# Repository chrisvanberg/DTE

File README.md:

___
# DTE ( Digital Temperature Equipment )
[EPHEC](http://www.ephec.be/cours-du-jours/nos-formations/informatique-3) - 2016/17 - T207 Digital Electronics, signal management. - Group 05

## Team
- **Chris Van Waesberghe** ([contact@chris.be](mailto:contact@chrisv.be)) - JAVA
- **Nathan Dolinski** ([n.dolinski@students.ephec.be](n.dolinski@students.ephec.be)) - PROTEUS / EAGLE
- **Mathieu Rousseau** ([m.rousseau@students.ephec.be](m.rousseau@students.ephec.be)) - PROTEUS / EAGLE / CCS
- **Amélie Courtin** ([a.courtin@students.ephec.be](a.courtin@students.ephec.be)) - WELDS / JAVA

## Warning
**Digital Temperature Equipment** was a school project (2016/17). It may never be updated in the future. Use it a your own risk. However feel free to submit a pull request !

## How to launch the simulation
1. Prerequisites
    1. The latest [JAVA runtime](https://www.java.com/fr/download/) update installed
    1. [Proteus 8](https://www.labcenter.com/)
1. Preset
    1. Clone or download the project
    1. Build or [download](https://github.com/KeydownR/DTE/releases) the binaries of the DTE JAVA interface
    1. Download and install the [**RXTX library**](http://fizzed.com/oss/rxtx-for-java) on your computer
    1. Create a COM virtual pair (Ex. COM1<->COM2) using for example [**VSPE** (Windows)](http://www.lawyerment.com/downloads/Programming/Debugging_and_Tracing/Review_17462_index.htm)
1. Launching the simulation
    1. Launch the DTE Java interface
    1. Connect to one of the COM port that you have paired earlier
    1. Open the PROTEUS project
    1. Be sure that the PIC source code is `sonde2.hex` (Double clic on the PIC and check the value)
    1. Click on the RS232 connector and selec the other COM port that you have paired earlier
    1. Start the PROTEUS simulation
1. Test the simulation
    1. You can change the threshold temperature on the JAVA interface
    1. You can change the current temperature on PROTEUS by clicking on the `+ / -` near the temperature probe
    1. The green led indicate that everything is fine
    1. The blinking red led indicate that the current temperature is beyond the threshold and an alert is triggered

## Licence

Copyright 2017
- [**Chris Van Waesberghe**](mailto:contact@chrisv.be) - JAVA
- [**Nathan Dolinski**](mailto:n.dolinski@students.ephec.be) - PROTEUS / EAGLE
- [**Mathieu Rousseau**](mailto:m.rousseau@students.ephec.be) - PROTEUS / EAGLE / CCS
- [**Amélie Courtin**](mailto:a.courtin@students.ephec.be) - WELDS / JAVA

The DTE Java Interface (and other components of the project) are free software: you can redistribute it and/or modify it under the terms of the GNU General Public License as published by the Free Software Foundation, either version 3 of the License, or (at your option) any later version. The DTE Java Interface is distributed in the hope that it will be useful, but WITHOUT ANY WARRANTY; without even the implied warranty of MERCHANTABILITY or FITNESS FOR A PARTICULAR PURPOSE.  See the GNU General Public License for more details.

You should have received a copy of the GNU General Public License along with the DTE Java Interface and the whole DTE Project.  If not, see <http://www.gnu.org/licenses/>.

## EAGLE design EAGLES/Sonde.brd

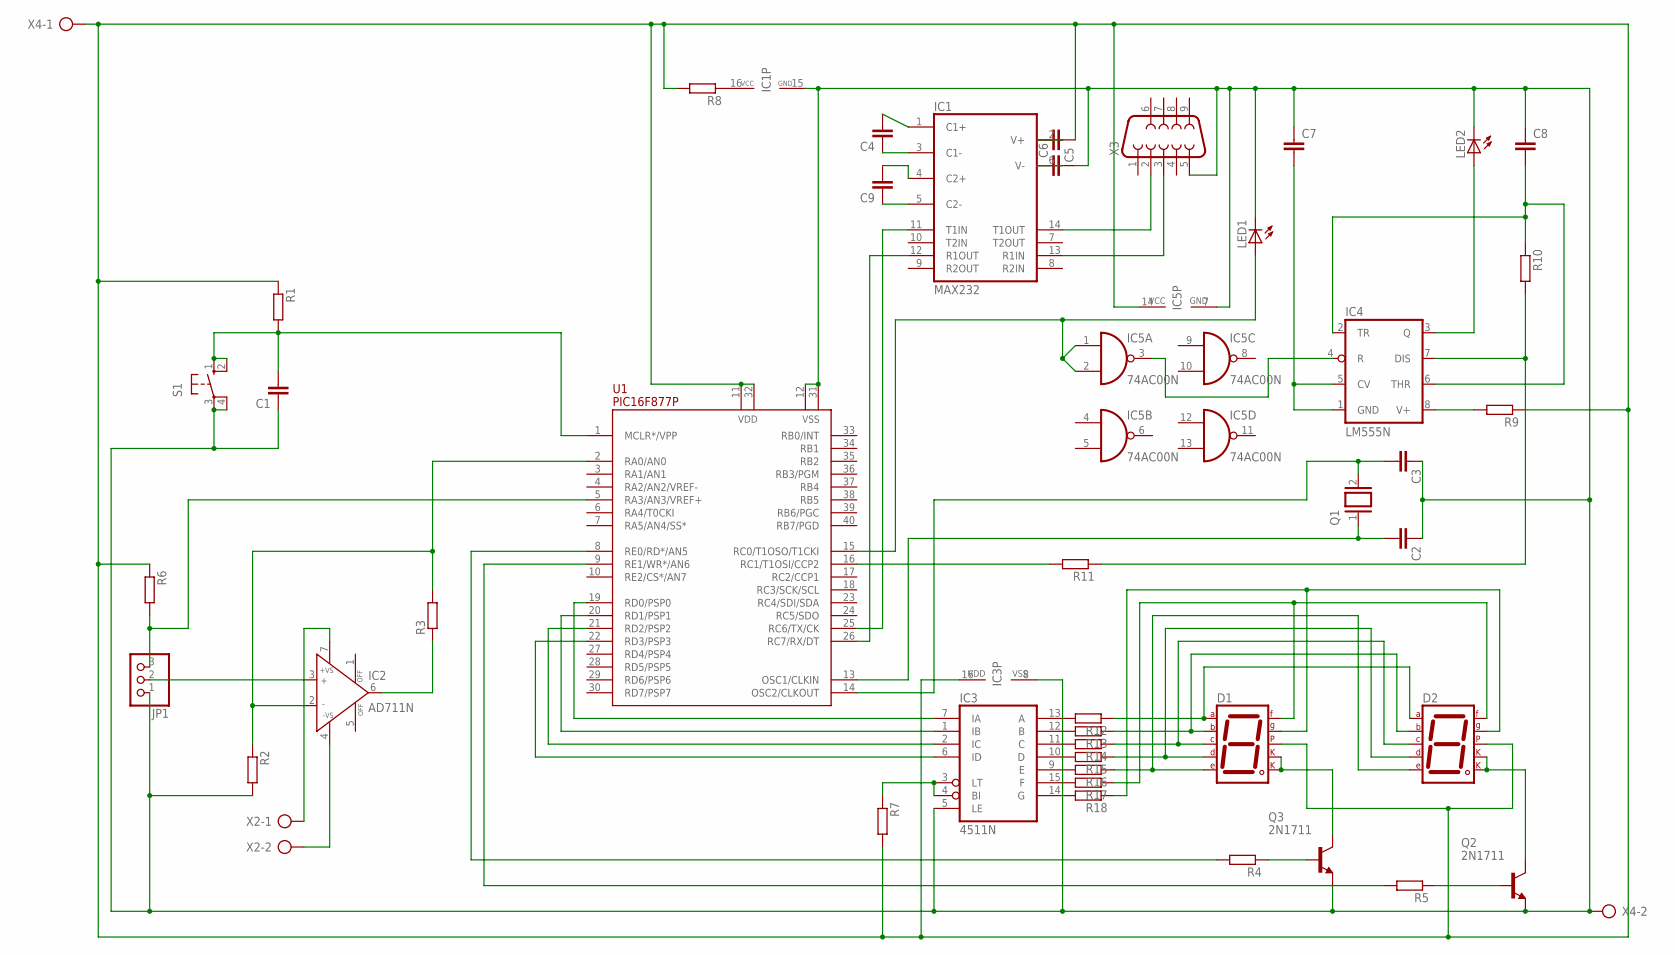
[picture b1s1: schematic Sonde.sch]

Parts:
C1, C2, C3, C4, C5, C6, C7, C8, C9: C-EU025-024X044; C025-024X044
D1, D2: 7SEG-CK; 7SEG-13
IC1: MAX232; DIL16
IC2: AD711N; DIL08
IC3: 4511N; DIL16
IC4: LM555N; DIL08
IC5: 74AC00N; DIL14
JP1: PINHD-1X3; 1X03
LED1, LED2: LED_ELD260; LED_LD260
Q1: XTAL/S; QS
Q2, Q3: 2N1711; TO39
R1, R2, R3, R4, R5, R6, R7, R8, R9, R10, R11, R12, R13, R14, R15, R16, R17, R18: R-EU_0207/10; 0207/10
S1: 10-XX; B3F-10XX
U1: PIC16F877P; DIL40
X2, X4: AK300/2
X3: F09V

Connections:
GND: C1.1, C2.1, C3.1, C6.2, C7.1, C8.1, IC1.15 (GND), IC3.5 (LE), IC3.8 (VSS), IC5.7 (GND), JP1.1, LED1.K (C), LED2.K (C), Q2.1 (E), Q3.1 (E), R2.2, S1.3, S1.4 (P1), U1.12 (VSS), U1.31 (VSS), X3.5, X4.2
unnamed: IC1.13 (R1IN), X3.3
unnamed: D2.3 (CK1), D2.8 (CK2), Q2.3 (C)
unnamed: IC4.4 (R), IC5.3 (O)
unnamed: C2.2, Q1.1, U1.13 (OSC1/CLKIN)
unnamed: IC2.3 (IN+), JP1.2
unnamed: D1.3 (CK1), D1.8 (CK2), Q3.3 (C)
unnamed: IC2.2 (IN-), R2.1, R3.2, U1.2 (RA0/AN0)
unnamed: Q3.2 (B), R4.1
unnamed: Q2.2 (B), R5.1
unnamed: R4.2, U1.8 (RE0/RD*/AN5)
unnamed: R5.2, U1.9 (RE1/WR*/AN6)
unnamed: D1.7 (A), D2.7 (A), R12.1
unnamed: C5.2, IC1.2 (V+)
unnamed: D1.6 (B), D2.6 (B), R13.1
unnamed: D1.4 (C), D2.4 (C), R14.1
unnamed: D1.2 (D), D2.2 (D), R15.1
unnamed: D1.1 (E), D2.1 (E), R16.1
unnamed: C6.1, IC1.6 (V-)
unnamed: D1.9 (F), D2.9 (F), R17.1
unnamed: IC1.11 (T1IN), U1.25 (RC6/TX/CK)
unnamed: D1.10 (G), D2.10 (G), R18.1
unnamed: IC1.12 (R1OUT), U1.26 (RC7/RX/DT)
unnamed: IC2.4 (-VS), X2.2
unnamed: IC2.6 (OUT), R3.1
unnamed: C9.2, IC1.4 (C2+)
unnamed: IC3.3 (LT), IC3.4 (BI), R7.1
unnamed: IC1.14 (T1OUT), X3.2
unnamed: IC3.7 (IA), U1.19 (RD0/PSP0)
unnamed: IC3.1 (IB), U1.20 (RD1/PSP1)
unnamed: IC3.2 (IC), U1.21 (RD2/PSP2)
unnamed: IC3.6 (ID), U1.22 (RD3/PSP3)
unnamed: C4.1, IC1.3 (C1-)
unnamed: C4.2, IC1.1 (C1+)
unnamed: R11.2, U1.16 (RC1/T1OSI/CCP2)
unnamed: IC1.16 (VCC), R8.1
unnamed: C7.2, IC4.1 (GND), IC4.5 (CV)
unnamed: IC4.8 (V+), R9.2
unnamed: IC4.3 (Q), LED2.A
unnamed: C1.2, R1.2, S1.1 (S), S1.2 (S1), U1.1 (MCLR*/VPP)
unnamed: C3.2, Q1.2, U1.14 (OSC2/CLKOUT)
unnamed: IC2.7 (+VS), X2.1
unnamed: C5.1, D1.5 (DP), D2.5 (DP), IC3.16 (VDD), IC5.14 (VCC), R1.1, R6.1, R7.2, R8.2, R9.1, U1.11 (VDD), U1.32 (VDD), X4.1
unnamed: C9.1, IC1.5 (C2-)
unnamed: IC3.13 (A), R12.2
unnamed: IC3.12 (B), R13.2
unnamed: IC3.11 (C), R14.2
unnamed: IC3.10 (D), R15.2
unnamed: IC3.9 (E), R16.2
unnamed: IC3.15 (F), R17.2
unnamed: IC3.14 (G), R18.2
unnamed: JP1.3, R6.2, U1.5 (RA3/AN3/VREF+)
unnamed: IC4.7 (DIS), R10.2, R11.1
unnamed: IC5.1 (I0), IC5.2 (I1), LED1.A, U1.15 (RC0/T1OSO/T1CKI)
unnamed: C8.2, IC4.2 (TR), IC4.6 (THR), R10.1

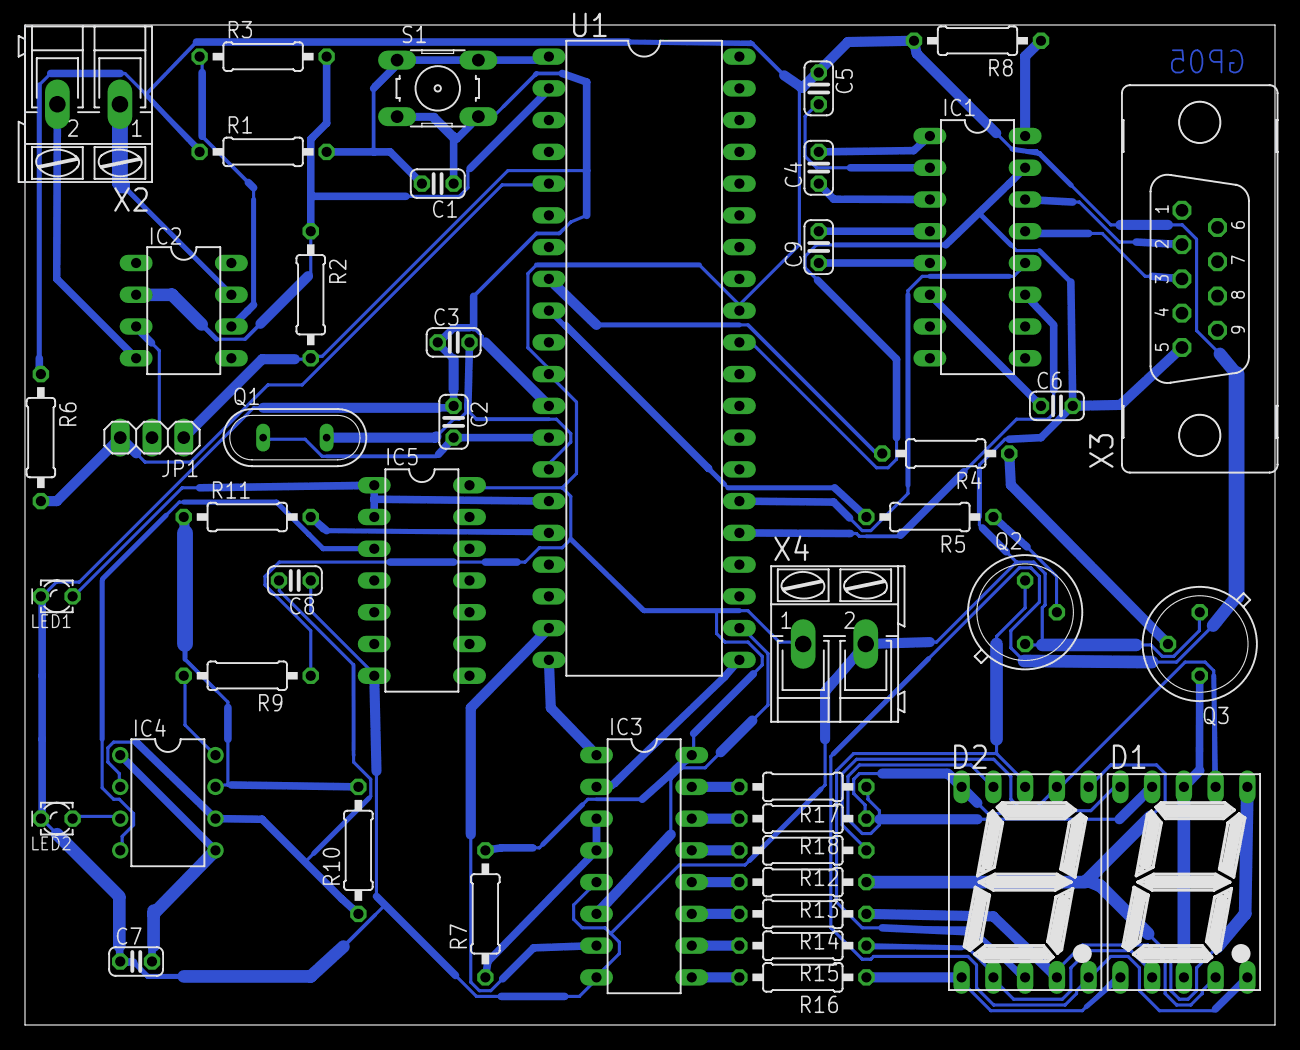
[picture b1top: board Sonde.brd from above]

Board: 2 copper layers, 100.0 x 80.0 mm, 45 parts (0 on the bottom side), 55 nets.

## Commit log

2017-02-09 Le montage du cour + datasheet
2017-02-09 DataSheet
2017-02-12 Mise à jour des consignes du projet
2017-02-14 Le thermomètre fonctionne sur les afficheurs 7 segments
    Les leds d'état reste à implémenter
    Le programme semble un peu lent du coup les températures ne s'affichent pas très bien.Elles alternent entre la température et 0.
    La connexion RS232 n'a pas été testée.
2017-02-14 Affichage clean grâce à une petite formule de ma composition
2017-02-16 INITIAL COMMIT - Java Interface
2017-02-17 Gitignore update
2017-02-17 MVC Architecture
2017-02-27 Rs232 testé + Schéma Eagle incomplet
    555 a cablé + led rouge et verte à trouvé et cablé + eventuellemnt recablé pour résultat plus propre
2017-02-28 Schéma eagle complet (nécessite probables corrections)
2017-02-28 Push sur master
2017-03-01 Library added
2017-03-01 MVC Implementation Ready
2017-03-01 Main package refactoring
2017-03-01 Lib update
2017-03-01 Lib cleaning
2017-03-01 Application sample
2017-03-01 Cleaning up the mockup and Javadoc comments
2017-03-01 Test update
2017-03-01 Cleaning up the code, something went wrong
2017-03-01 Recopying the code
2017-03-01 Javadoc Update
2017-03-01 Update of the code
2017-03-01 Model constructor and instance vriables
2017-03-02 MVC Pattern now working proprely
2017-03-02 Adding private to all instance variables
2017-03-02 Adding the test classes
2017-03-02 License Update and Indent
2017-03-02 Adding Jansi Lib for the CLIView
2017-03-03 Model update. Manage a list of all the previous temperatures
2017-03-03 Cleaning up master branch
2017-03-03 Creating separate folders
2017-03-03 Separate folders
2017-03-03 Deleting .empty file since there is something in the folder
2017-03-03 Deleting .empty file
2017-03-03 LICENSE and README back in root folder
2017-03-03 Correction of Nathan's name and email
2017-03-03 License update (MIT -> GPL3)
2017-03-03 add C code of this morning
2017-03-03 Model Update and adding exception
2017-03-03 Model Test updated
2017-03-03 clean proteus schema
2017-03-04 Code Refactoring. Model have now all the signatures needed
2017-03-04 Model's Test Are done
2017-03-04 Model Update. Now use Constant for alertLevel
2017-03-04 ModelTest now use AlertLevelConstant for the test
2017-03-04 Adding javadoc comment for AlertLevel constants
2017-03-04 AlertLevel constant updated
2017-03-04 Implementation & Test update
2017-03-06 Correction du nom de Nathan dans les copyrights
2017-03-06 Le schéma eagle
2017-03-06 L'ampli-op est alimenté
2017-03-06 Le board
2017-03-07 Board entièrement bottom layer
2017-03-08 board and schema optimisations - wip
2017-03-08 ajout du bornier (pour le +10/-10V)
2017-03-09 Board fini
2017-03-10 correction du schéma eagle
2017-03-10 correction du schéma eagle - ajout du bornier pour le 5V/Ground
2017-03-10 correction du schéma eagle - connection du PIC au bornier
2017-03-10 correction du schéma eagle - Patte 5 du RS232 au ground
2017-03-10 98% routing and one orphan wire
2017-03-10 100% routing
2017-03-11 grossissement des pistes
2017-03-11 ajout du plan de masse et du numéro de groupe
2017-03-11 correction de 3 routes dont 1 critique
2017-03-11 erreurs corrigées
2017-03-12 correction du plan de masse, isolate = 0.024
2017-05-03 init
2017-05-03 minor fix + comments
2017-05-03 minor fix
2017-05-05 fix + compile
2017-05-10 ModelTest completed and passed
2017-05-10 GUI view design finished
2017-05-10 Model fixed with tests
2017-05-10 CLIView is not showed for the moment
2017-05-10 RXTX test
2017-05-10 The app list all the COM Port avaliable
2017-05-12 fix c wip, have to test with java
2017-05-12 fix c, should work now
2017-05-13 Model update
2017-05-13 To delete later
2017-05-13 Start the real thing
2017-05-14 The app connect to a selected COM PORT
2017-05-14 The app react to the currentTemp and thresolhd Temp
2017-05-14 checkAlertLevel fixed to avoid false positive
2017-05-14 serialWriter implemented but not fonctional
2017-05-14 This should work
2017-05-15 Pre-release
2017-05-15 interruption listener, sends temperature on change
2017-05-15 New threshold sent only on change
2017-05-15 Update message updated
2017-05-15 Testing if the SerialWriter is needed
2017-05-15 Refactoring
2017-05-15 pre-release v1.0
2017-05-15 Javadoc update "pre-release v1.0"
2017-05-15 Gitignore update to avoid some PROTEUS temp file
2017-05-15 Updating the gitignore to avoid the history of proteus
2017-05-15 Design update
2017-05-18 Package Name update
2017-05-18 JAVADOC update - New package name
2017-08-03 Adding resources
